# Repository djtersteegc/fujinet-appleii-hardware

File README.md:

Hardware variants for the Apple II FujiNet platform (FujiApple).

Still a work in progress...

# DevKit IDC-20

Interactive BOM - [https://djtersteegc.github.io/fujinet-appleii-hardware/ibom-DevKit-IDC-20-v1.0.html](https://djtersteegc.github.io/fujinet-appleii-hardware/ibom-DevKit-IDC-20-v1.0.html)

# DevKit SmartPort

Interactive BOM - [https://djtersteegc.github.io/fujinet-appleii-hardware/ibom-DevKit-SmartPort-v1.0.html](https://djtersteegc.github.io/fujinet-appleii-hardware/ibom-DevKit-SmartPort-v1.0.html)

# DevKit Combo

Interactive BOM - [https://djtersteegc.github.io/fujinet-appleii-hardware/ibom-DevKit-Combo-v1.0.html](https://djtersteegc.github.io/fujinet-appleii-hardware/ibom-DevKit-Combo-v1.0.html)

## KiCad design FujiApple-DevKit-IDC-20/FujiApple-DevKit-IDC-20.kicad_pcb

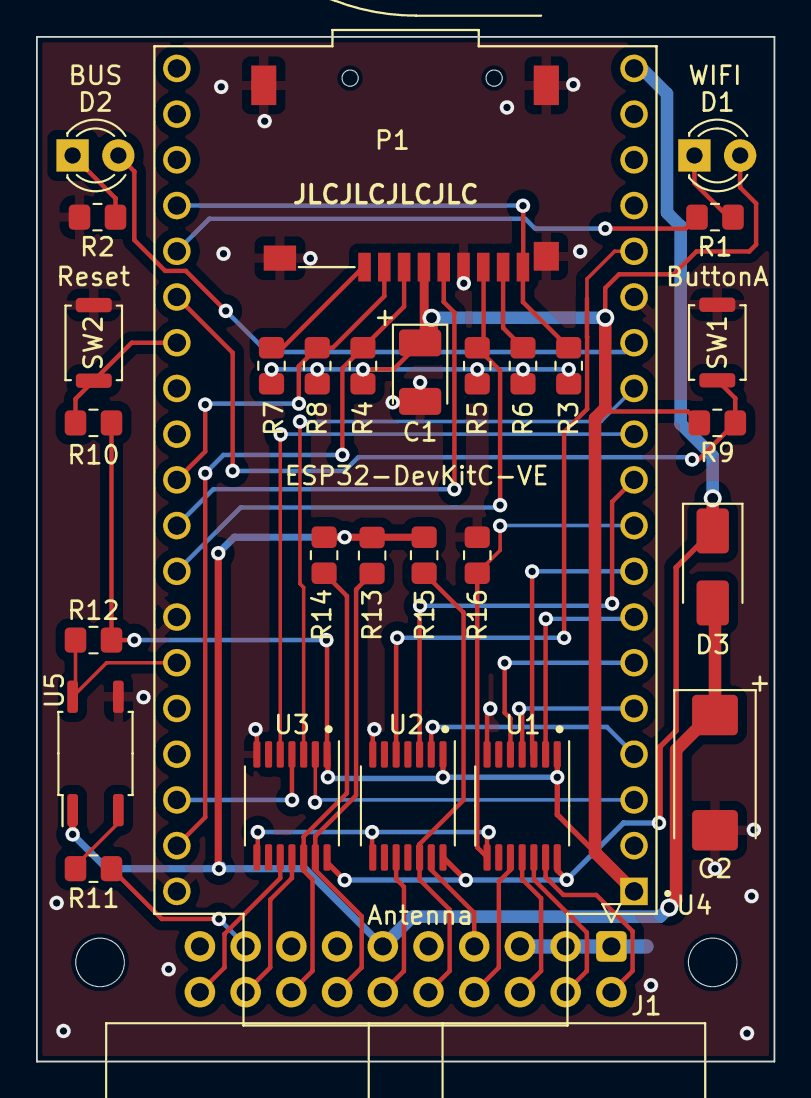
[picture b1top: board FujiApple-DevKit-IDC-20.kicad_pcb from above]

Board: 2 copper layers, 41.0 x 56.9 mm, 32 parts (0 on the bottom side), 43 nets.

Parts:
C1: 47uF 10v; CP_EIA-3528-15_AVX-H_Pad1.50x2.35mm_HandSolder
C2: 47uF 10v; CP_EIA-7343-30_AVX-N_Pad2.25x2.55mm_HandSolder
D1: WIFI; LED_D3.0mm
D2: BUS; LED_D3.0mm
D3: B140-E3; D_SMA
H1, H2: MountingHole; MountingHole_2.7mm_M2.5
J1: Conn_02x10_Odd_Even; IDC-Header_2x10_P2.54mm_Horizontal
P1: ST-TF-003A; SUNTECH_ST-TF-003A
R1, R13, R14, R15: 1K; R_0805_2012Metric_Pad1.20x1.40mm_HandSolder
R2: 1.2K; R_0805_2012Metric_Pad1.20x1.40mm_HandSolder
R3, R4, R5, R6, R7, R8, R9, R10, R12, R16: 10K; R_0805_2012Metric_Pad1.20x1.40mm_HandSolder
R11: 270R; R_0805_2012Metric_Pad1.20x1.40mm_HandSolder
SW1: ButtonA; SW_Push_SPST_NO_Alps_SKRK
SW2: Reset; SW_Push_SPST_NO_Alps_SKRK
U1, U2, U3: LSF0204DPWR; TSSOP-14_4.4x5mm_P0.65mm
U4: ESP32-DevKitC-VE; MODULE_ESP32-DEVKITC-32U
U5: SFH690AT; SO-4_4.4x3.9mm_P2.54mm

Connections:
+3.3V: C1.1, D1.2 (A), P1.4 (VDD), R3.2, R4.2, R5.2, R6.2, R7.2, R8.2, R9.2, R10.2, R12.2, U1.1 (VREF_A), U2.1 (VREF_A), U3.1 (VREF_A), U4.1 (3V3)
+5V: D3.1 (K), U1.14 (VREF_B), U2.14 (VREF_B), U3.14 (VREF_B), U4.19 (EXT_5V)
/A2_5V: C2.1, D3.2 (A), J1.11, R13.2, R14.2, R15.2, U5.1
/A2_DRIVE1: J1.14, R13.1, U3.13 (B1)
/A2_EN3.5: J1.7, U2.13 (B1)
/A2_HDSEL: J1.12, U2.10 (B4)
/A2_PH0: J1.2, U1.13 (B1)
/A2_PH1: J1.4, U1.12 (B2)
/A2_PH2: J1.6, U1.11 (B3)
/A2_PH3: J1.8, U1.10 (B4)
/A2_RD_DATA: J1.16, R14.1, U3.12 (B2)
/A2_WPROT: J1.20, U3.10 (B4)
/A2_WREQ: J1.10, R15.1, U2.12 (B2)
/A2_WR_DATA: J1.18, U3.11 (B3)
/DRIVE2: J1.17, R11.1
/IO0: R9.1, SW1.1 (A), U4.25 (IO0)
/IO2/WIFI_LED: R1.2, U4.24 (IO2)
/IO4/SAFE_RESET: R10.1, SW2.1 (A), U4.26 (IO4)
/IO5/SPI_CS: P1.2 (DAT3), R8.1, U4.29 (IO5)
/IO12/BUS_LED: D2.2 (A), U4.13 (IO12)
/IO13/HDSEL: U2.5 (A4), U4.15 (IO13)
/IO14/RDDATA: U3.3 (A2), U4.12 (IO14)
/IO15/CD: P1.9 (CD), R3.1, U4.23 (IO15)
/IO18/SPI_CLK: P1.5 (CLK), U4.30 (IO18)
/IO19/SPI_MISO: P1.7 (DAT0), R5.1, U4.31 (IO19)
/IO21/DRV2: R12.1, U4.33 (IO21), U5.4
/IO22/WRDATA: U3.4 (A3), U4.36 (IO22)
/IO23/SPI_MOSI: P1.3 (CMD), R4.1, U4.37 (IO23)
/IO25/BUF_EN: R16.1, U1.8 (EN), U2.8 (EN), U3.8 (EN), U4.9 (IO25)
/IO26/WREQ: U2.3 (A2), U4.10 (IO26)
/IO27/WRPROT/ACK: U3.5 (A4), U4.11 (IO27)
/IO32/PH0/REQ: U1.2 (A1), U4.7 (IO32)
/IO33/PH1: U1.3 (A2), U4.8 (IO33)
/IO34/PH2: U1.4 (A3), U4.5 (IO34)
/IO35/PH3: U1.5 (A4), U4.6 (IO35)
/IO36/DRIVE1: U3.2 (A1), U4.3 (SENSOR_VP)
/IO39/EN3.5: U2.2 (A1), U4.4 (SENSOR_VN)
GND: C1.2, C2.2, J1.1, J1.3, J1.5, P1.6 (VSS), P1.G1 (GND), P1.G2 (GND), P1.G3 (GND), P1.G4 (GND), R2.2, R16.2, SW1.2 (B), SW2.2 (B), U1.7 (GND), U2.7 (GND), U3.7 (GND), U4.14 (GND1), U4.32 (GND2), U4.38 (GND3), U5.3
unnamed: D1.1 (K), R1.1
unnamed: D2.1 (K), R2.1
unnamed: P1.8 (DAT1), R6.1
unnamed: P1.1 (DAT2), R7.1
unnamed: R11.2, U5.2

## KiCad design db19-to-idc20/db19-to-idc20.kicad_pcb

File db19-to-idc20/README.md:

Complete docs soon...

Bulk pins - https://www.aliexpress.us/item/3256802431271655.html

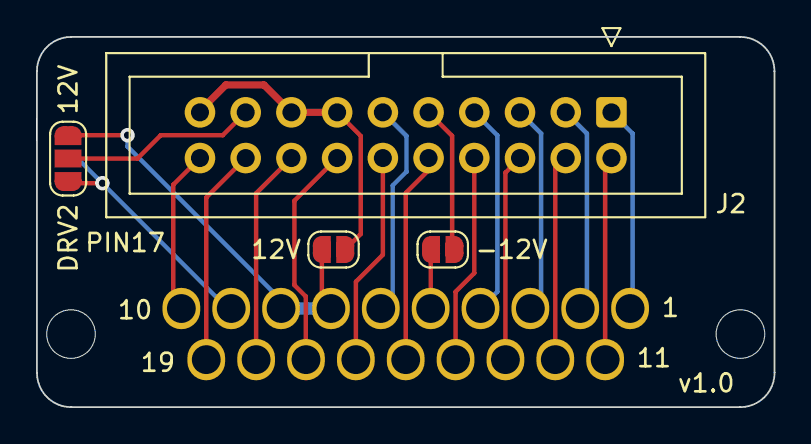
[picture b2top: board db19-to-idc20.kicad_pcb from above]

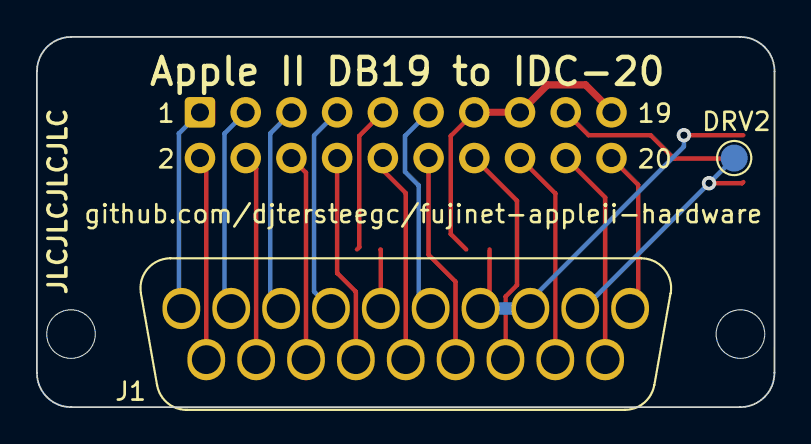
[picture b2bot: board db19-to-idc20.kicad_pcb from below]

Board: 2 copper layers, 41.0 x 20.6 mm, 6 parts (2 on the bottom side), 21 nets.

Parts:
J1: DB19_Plug; DSUB-19_Male_Vertical_P2.77x2.84mm_Narrow_MountingHoles_Ful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
J2: IDC-20; IDC-Header_2x10_P2.54mm_Vertical
JP1: -12V; SolderJumper-2_P1.3mm_Open_RoundedPad1.0x1.5mm
JP2: 12V; SolderJumper-2_P1.3mm_Open_RoundedPad1.0x1.5mm
JP4: PIN17; SolderJumper-3_P1.3mm_Open_RoundedPad1.0x1.5mm_NumberLabels
TP1: DRV2; TestPoint_Pad_D1.5mm

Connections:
/A2_5V: J1.6, J2.11
/A2_DRIVE1: J1.17, J2.14
/A2_EN3.5: J1.4, J2.7
/A2_HDSEL: J1.16, J2.12
/A2_PH0: J1.11, J2.2
/A2_PH1: J1.12, J2.4
/A2_PH2: J1.13, J2.6
/A2_PH3: J1.14, J2.8
/A2_RD_DATA: J1.18, J2.16
/A2_WPROT: J1.10, J2.20
/A2_WREQ: J1.15, J2.10
/A2_WR_DATA: J1.19, J2.18
/DB19_12V: J1.7, J1.8, JP2.1 (A), JP4.1 (A)
/DB19_DRIVE2: J1.9, JP4.3 (B), TP1.1
/GND1: J1.1, J2.1
/GND2: J1.2, J2.3
/GND3: J1.3, J2.5
/IDC20_12V: J2.13, J2.15, J2.19, JP2.2 (B)
/IDC_PIN17: J2.17, JP4.2 (C)
unnamed: J2.9, JP1.2 (B)
unnamed: J1.5, JP1.1 (A)

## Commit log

2024-01-10 V1.0 sent to the fab
2024-01-28 Add iBOM's
2024-01-31 Update 3D models and STL's. IDC-20 and DB19 adapter built and working.
2024-02-09 Add Combo version
2024-02-13 Add some DB19 adapter docs and pics
